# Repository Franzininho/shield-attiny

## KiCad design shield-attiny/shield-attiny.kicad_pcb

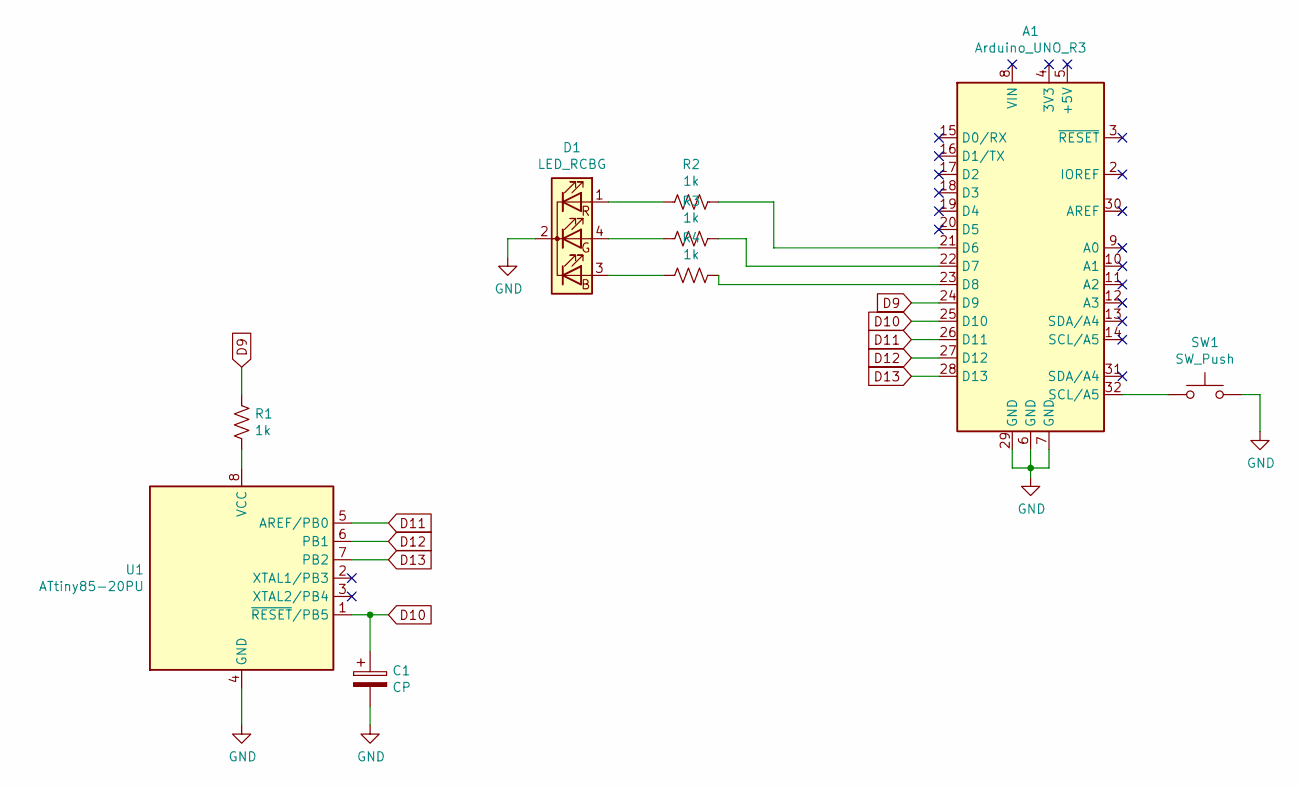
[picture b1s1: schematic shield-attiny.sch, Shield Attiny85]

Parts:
A1: Arduino_UNO_R3
C1: CP; CP_Radial_D6.3mm_P2.50mm
D1: LED_RCBG; LED_D5.0mm-4_RGB
R1, R2, R3, R4: 1k; R_Axial_DIN0207_L6.3mm_D2.5mm_P10.16mm_Horizontal
SW1: SW_Push; SW_PUSH_6mm_H7.3mm
U1: ATtiny85-20PU; DIP-8_W7.62mm

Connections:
D9: A1.24 (D9), R1.1
D10: A1.25 (D10), C1.1, U1.1 (~RESET~/PB5)
D11: A1.26 (D11), U1.5 (AREF/PB0)
D12: A1.27 (D12), U1.6 (PB1)
D13: A1.28 (D13), U1.7 (PB2)
GND: A1.6 (GND), A1.7 (GND), A1.29 (GND), C1.2, D1.2 (K), SW1.2, U1.4 (GND)
unnamed: A1.21 (D6), R2.1
unnamed: A1.22 (D7), R3.1
unnamed: A1.23 (D8), R4.1
unnamed: A1.32 (SCL/A5), SW1.1
unnamed: D1.1 (RA), R2.2
unnamed: D1.3 (BA), R4.2
unnamed: D1.4 (GA), R3.2
unnamed: R1.2, U1.8 (VCC)

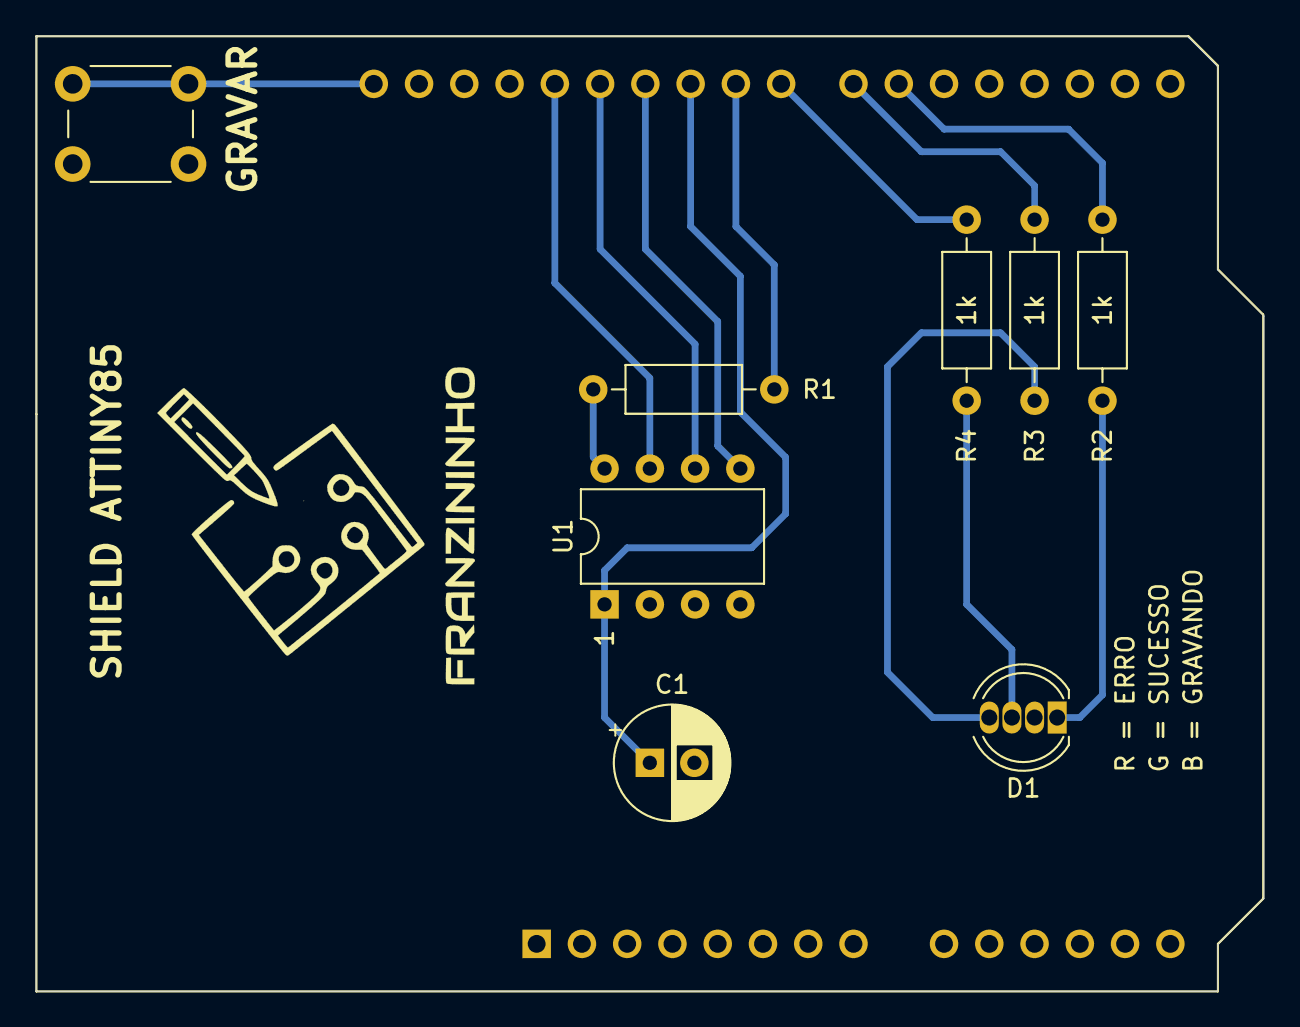
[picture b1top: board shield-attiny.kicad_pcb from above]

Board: 2 copper layers, 68.9 x 53.6 mm, 9 parts (0 on the bottom side), 14 nets.

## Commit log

2021-02-20 Adicionando arquivos do projeto
2021-02-20 Adicionando readme
2021-02-25 Adicionando v0 do layout
2021-03-10 Adiconando Layout
